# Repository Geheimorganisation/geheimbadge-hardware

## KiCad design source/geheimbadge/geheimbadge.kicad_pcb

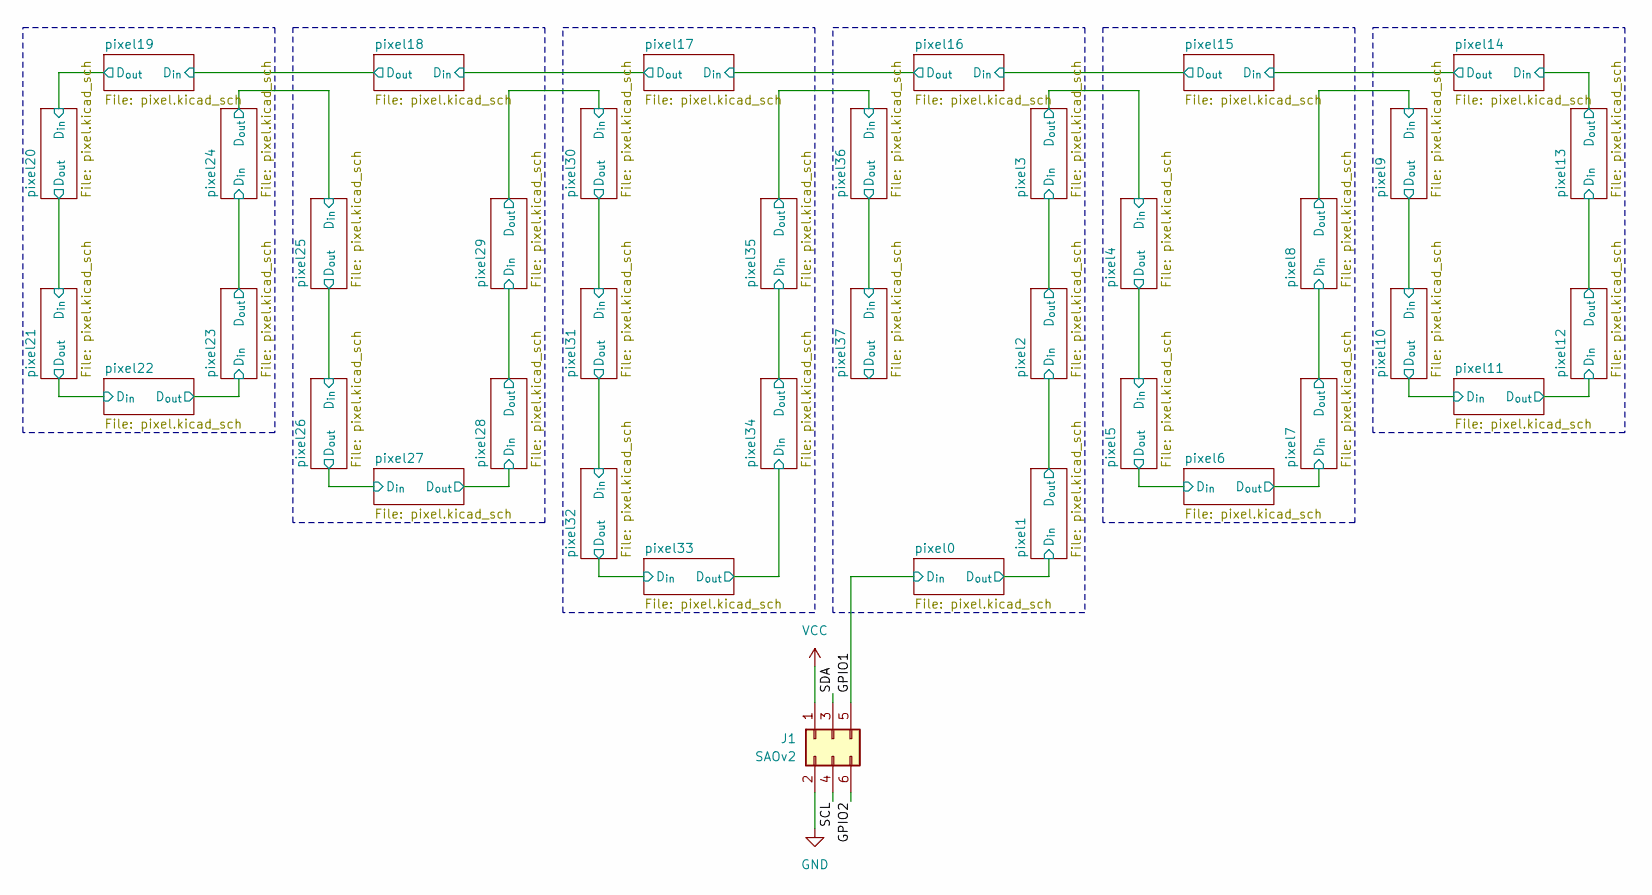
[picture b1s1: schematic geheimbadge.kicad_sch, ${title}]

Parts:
J1: SAOv2; IDC-Header_2x03_P2.54mm_Vertical_SMD; LCSC C4749176

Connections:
/GPIO1: J1.5; also elsewhere on the board
/GPIO2: J1.6
/SCL: J1.4
/SDA: J1.3
GND: J1.2; also elsewhere on the board
VCC: J1.1; also elsewhere on the board

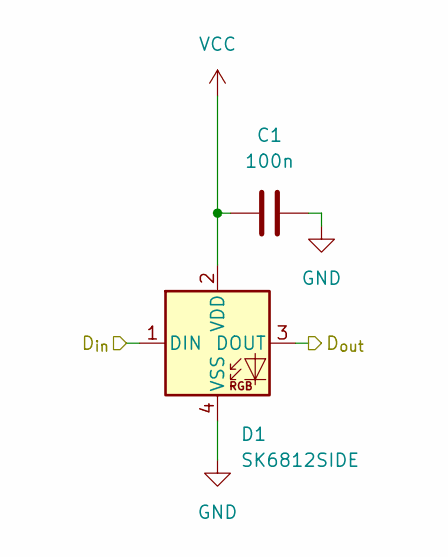
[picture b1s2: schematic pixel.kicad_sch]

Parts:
C1: 100n; C_0402_1005Metric; LCSC C1525
D1: SK6812SIDE; LED-SMD_4P-L4.0-W1.6-L; LCSC C5378721

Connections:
/GPIO1: D1.1 (DIN); also elsewhere on the board
/pixel0/D_{out}: D1.3 (DOUT); also elsewhere on the board
GND: C1.2, D1.4 (VSS); also elsewhere on the board
VCC: C1.1, D1.2 (VDD); also elsewhere on the board

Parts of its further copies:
C2, C3, C4, C5, C6, C7, C8, C9, C10, C11, C12, C13, C14, C15, C16, C17, C18, C19, C20, C21, C22, C23, C24, C25, C26, C27, C28, C29, C30, C31, C32, C33, C34, C35, C36, C37, C38: 100n; C_0402_1005Metric; LCSC C1525
D2, D3, D4, D5, D6, D7, D8, D9, D10, D11, D12, D13, D14, D15, D16, D17, D18, D19, D20, D21, D22, D23, D24, D25, D26, D27, D28, D29, D30, D31, D32, D33, D34, D35, D36, D37, D38: SK6812SIDE; LED-SMD_4P-L4.0-W1.6-L; LCSC C5378721

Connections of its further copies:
/pixel0/D_{out}: D2.1 (DIN); also elsewhere on the board
/pixel1/D_{out}: D2.3 (DOUT), D3.1 (DIN)
/pixel2/D_{out}: D3.3 (DOUT), D4.1 (DIN)
/pixel3/D_{out}: D4.3 (DOUT), D5.1 (DIN)
/pixel4/D_{out}: D5.3 (DOUT), D6.1 (DIN)
/pixel5/D_{out}: D6.3 (DOUT), D7.1 (DIN)
/pixel6/D_{out}: D7.3 (DOUT), D8.1 (DIN)
/pixel7/D_{out}: D8.3 (DOUT), D9.1 (DIN)
/pixel8/D_{out}: D9.3 (DOUT), D10.1 (DIN)
/pixel10/D_{in}: D10.3 (DOUT), D11.1 (DIN)
/pixel10/D_{out}: D11.3 (DOUT), D12.1 (DIN)
/pixel11/D_{out}: D12.3 (DOUT), D13.1 (DIN)
/pixel12/D_{out}: D13.3 (DOUT), D14.1 (DIN)
/pixel13/D_{out}: D14.3 (DOUT), D15.1 (DIN)
/pixel14/D_{out}: D15.3 (DOUT), D16.1 (DIN)
/pixel15/D_{out}: D16.3 (DOUT), D17.1 (DIN)
/pixel16/D_{out}: D17.3 (DOUT), D18.1 (DIN)
/pixel17/D_{out}: D18.3 (DOUT), D19.1 (DIN)
/pixel18/D_{out}: D19.3 (DOUT), D20.1 (DIN)
/pixel19/D_{out}: D20.3 (DOUT), D21.1 (DIN)
/pixel20/D_{out}: D21.3 (DOUT), D22.1 (DIN)
/pixel21/D_{out}: D22.3 (DOUT), D23.1 (DIN)
/pixel22/D_{out}: D23.3 (DOUT), D24.1 (DIN)
/pixel23/D_{out}: D24.3 (DOUT), D25.1 (DIN)
/pixel24/D_{out}: D25.3 (DOUT), D26.1 (DIN)
/pixel25/D_{out}: D26.3 (DOUT), D27.1 (DIN)
/pixel26/D_{out}: D27.3 (DOUT), D28.1 (DIN)
/pixel27/D_{out}: D28.3 (DOUT), D29.1 (DIN)
/pixel28/D_{out}: D29.3 (DOUT), D30.1 (DIN)
/pixel29/D_{out}: D30.3 (DOUT), D31.1 (DIN)
/pixel30/D_{out}: D31.3 (DOUT), D32.1 (DIN)
/pixel31/D_{out}: D32.3 (DOUT), D33.1 (DIN)
/pixel32/D_{out}: D33.3 (DOUT), D34.1 (DIN)
/pixel33/D_{out}: D34.3 (DOUT), D35.1 (DIN)
/pixel34/D_{out}: D35.3 (DOUT), D36.1 (DIN)
/pixel35/D_{out}: D36.3 (DOUT), D37.1 (DIN)
/pixel36/D_{out}: D37.3 (DOUT), D38.1 (DIN)
/pixel37/D_{out}: D38.3 (DOUT)
GND: C2.2, C3.2, C4.2, C5.2, C6.2, C7.2, C8.2, C9.2, C10.2, C11.2, C12.2, C13.2, C14.2, C15.2, C16.2, C17.2, C18.2, C19.2, C20.2, C21.2, C22.2, C23.2, C24.2, C25.2, C26.2, C27.2, C28.2, C29.2, C30.2, C31.2, C32.2, C33.2, C34.2, C35.2, C36.2, C37.2, C38.2, D2.4 (VSS), D3.4 (VSS), D4.4 (VSS), D5.4 (VSS), D6.4 (VSS), D7.4 (VSS), D8.4 (VSS), D9.4 (VSS), D10.4 (VSS), D11.4 (VSS), D12.4 (VSS), D13.4 (VSS), D14.4 (VSS), D15.4 (VSS), D16.4 (VSS), D17.4 (VSS), D18.4 (VSS), D19.4 (VSS), D20.4 (VSS), D21.4 (VSS), D22.4 (VSS), D23.4 (VSS), D24.4 (VSS), D25.4 (VSS), D26.4 (VSS), D27.4 (VSS), D28.4 (VSS), D29.4 (VSS), D30.4 (VSS), D31.4 (VSS), D32.4 (VSS), D33.4 (VSS), D34.4 (VSS), D35.4 (VSS), D36.4 (VSS), D37.4 (VSS), D38.4 (VSS); also elsewhere on the board
VCC: C2.1, C3.1, C4.1, C5.1, C6.1, C7.1, C8.1, C9.1, C10.1, C11.1, C12.1, C13.1, C14.1, C15.1, C16.1, C17.1, C18.1, C19.1, C20.1, C21.1, C22.1, C23.1, C24.1, C25.1, C26.1, C27.1, C28.1, C29.1, C30.1, C31.1, C32.1, C33.1, C34.1, C35.1, C36.1, C37.1, C38.1, D2.2 (VDD), D3.2 (VDD), D4.2 (VDD), D5.2 (VDD), D6.2 (VDD), D7.2 (VDD), D8.2 (VDD), D9.2 (VDD), D10.2 (VDD), D11.2 (VDD), D12.2 (VDD), D13.2 (VDD), D14.2 (VDD), D15.2 (VDD), D16.2 (VDD), D17.2 (VDD), D18.2 (VDD), D19.2 (VDD), D20.2 (VDD), D21.2 (VDD), D22.2 (VDD), D23.2 (VDD), D24.2 (VDD), D25.2 (VDD), D26.2 (VDD), D27.2 (VDD), D28.2 (VDD), D29.2 (VDD), D30.2 (VDD), D31.2 (VDD), D32.2 (VDD), D33.2 (VDD), D34.2 (VDD), D35.2 (VDD), D36.2 (VDD), D37.2 (VDD), D38.2 (VDD); also elsewhere on the board

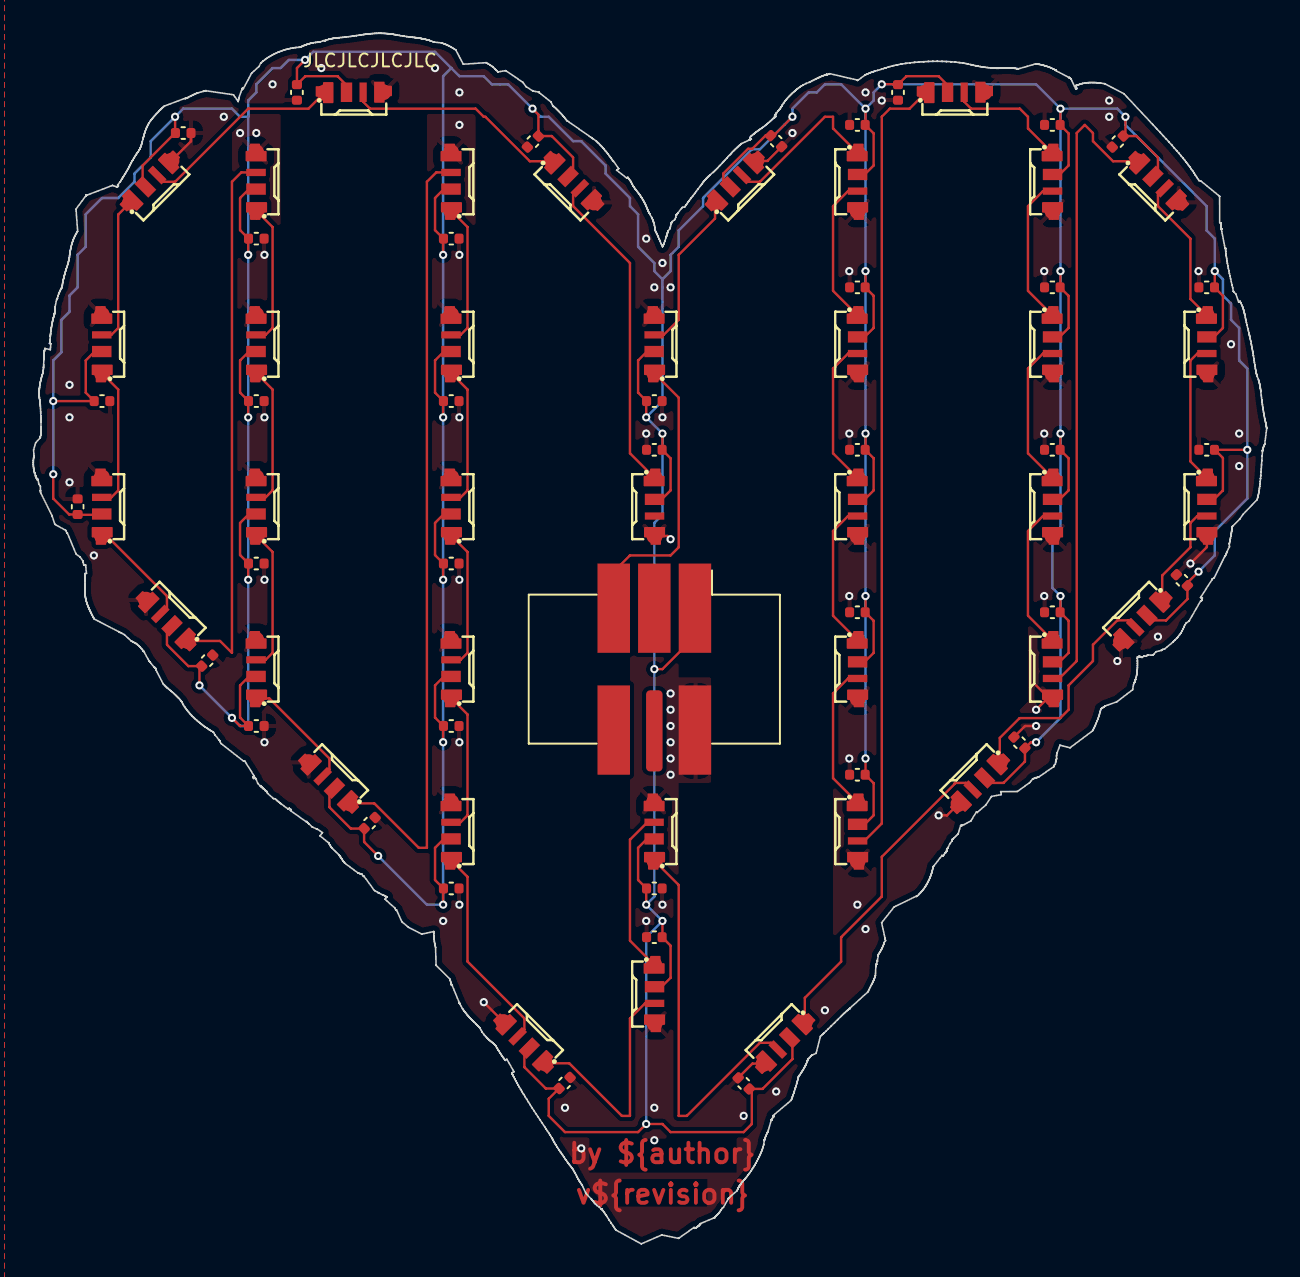
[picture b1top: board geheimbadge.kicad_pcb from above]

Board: 2 copper layers, 75.9 x 74.5 mm, 77 parts (0 on the bottom side), 40 nets.

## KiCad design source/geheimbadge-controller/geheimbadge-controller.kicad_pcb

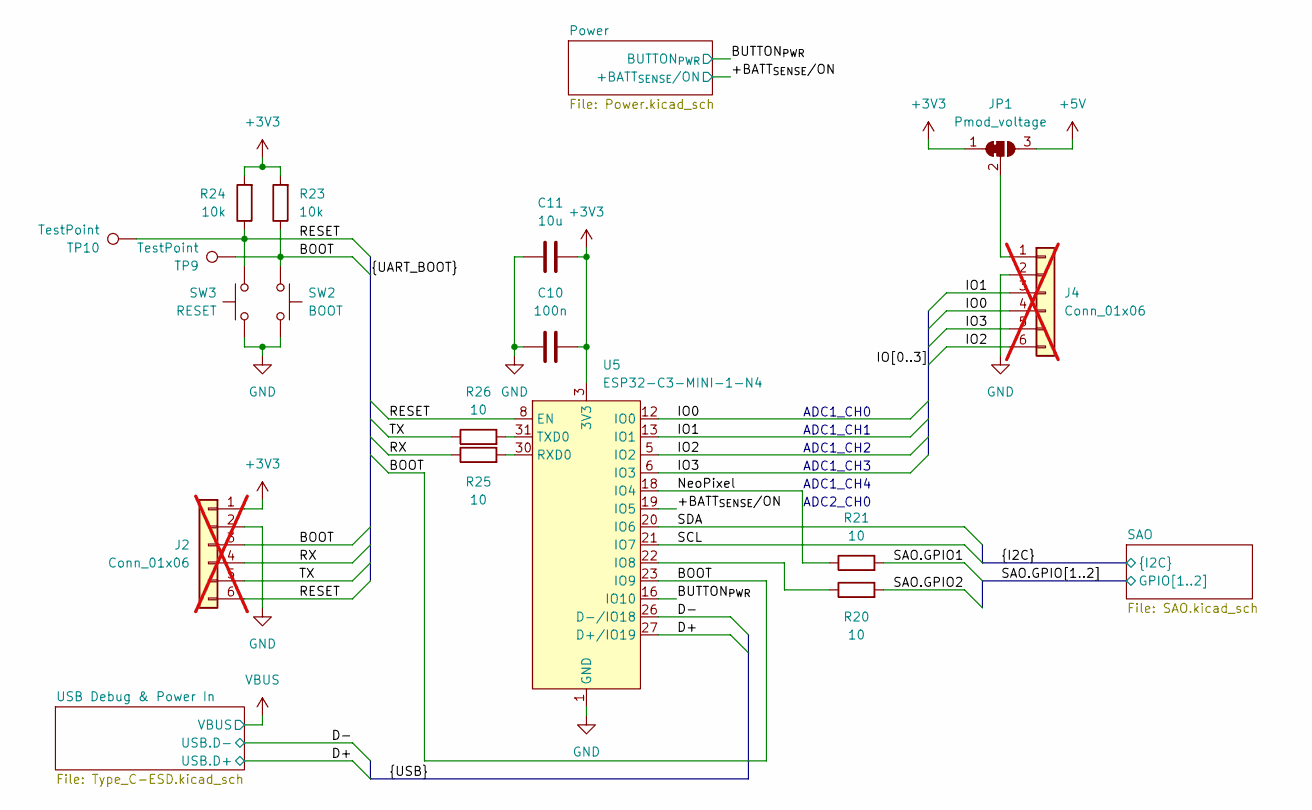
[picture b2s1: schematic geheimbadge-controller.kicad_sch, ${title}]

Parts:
C10: 100n; C_0603_1608Metric; LCSC Part C14663
C11: 10u; C_0805_2012Metric; LCSC Part C15850
J2, J4: Conn_01x06; PinSocket_1x06_P2.54mm_Horizontal; not fitted
JP1: Pmod_voltage; SolderJumper-3_P1.3mm_Bridged12_RoundedPad1.0x1.5mm
R20, R21, R25, R26: 10; R_0603_1608Metric; LCSC Part C22859
R23, R24: 10k; R_0603_1608Metric; LCSC Part C25804
SW2: BOOT; SW_Push_1P1T_XKB_TS-1187A; LCSC Part C318884
SW3: RESET; SW_Push_1P1T_XKB_TS-1187A; LCSC Part C318884
TP9, TP10: TestPoint; TestPoint_Pad_D1.0mm
U5: ESP32-C3-MINI-1-N4; WIFIM-SMD_ESP32-C3-MINI-1; LCSC Part C2838502

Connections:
+3V3: C10.1, C11.1, J2.1, JP1.1 (A), R23.2, R24.2, U5.3 (3V3); also elsewhere on the board
+5V: JP1.3 (B); also elsewhere on the board
/+BATT_{SENSE}/ON: U5.19 (IO5); also elsewhere on the board
/BOOT: J2.3, R23.1, SW2.2, TP9.1, U5.23 (IO9)
/BUTTON_{PWR}: U5.16 (IO10); also elsewhere on the board
/D+: U5.27 (D+/IO19); also elsewhere on the board
/D-: U5.26 (D-/IO18); also elsewhere on the board
/IO0: J4.4, U5.12 (IO0)
/IO1: J4.3, U5.13 (IO1)
/IO2: J4.6, U5.5 (IO2)
/IO3: J4.5, U5.6 (IO3)
/NeoPixel: R21.1, U5.18 (IO4)
/RESET: J2.6, R24.1, SW3.2, TP10.1, U5.8 (EN)
/RX: J2.4, R25.1
/SAO.GPIO1: R21.2; also elsewhere on the board
/SAO.GPIO2: R20.2; also elsewhere on the board
/SCL: U5.21 (IO7); also elsewhere on the board
/SDA: U5.20 (IO6); also elsewhere on the board
/TX: J2.5, R26.1
GND: C10.2, C11.2, J2.2, J4.2, SW2.1, SW3.1, U5.1 (GND), U5.2 (GND), U5.11 (GND), U5.14 (GND), U5.36 (GND), U5.37 (GND), U5.38 (GND), U5.39 (GND), U5.40 (GND), U5.41 (GND), U5.42 (GND), U5.43 (GND), U5.44 (GND), U5.45 (GND), U5.46 (GND), U5.47 (GND), U5.48 (GND), U5.49 (GND), U5.50 (GND), U5.51 (GND), U5.52 (GND), U5.53 (GND); also elsewhere on the board
unnamed: J4.1, JP1.2 (C)
unnamed: R20.1, U5.22 (IO8)
unnamed: R25.2, U5.30 (RXD0)
unnamed: R26.2, U5.31 (TXD0)

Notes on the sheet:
ADC2_CH0
ADC1_CH2
ADC1_CH1
ADC1_CH3
ADC1_CH0
ADC1_CH4

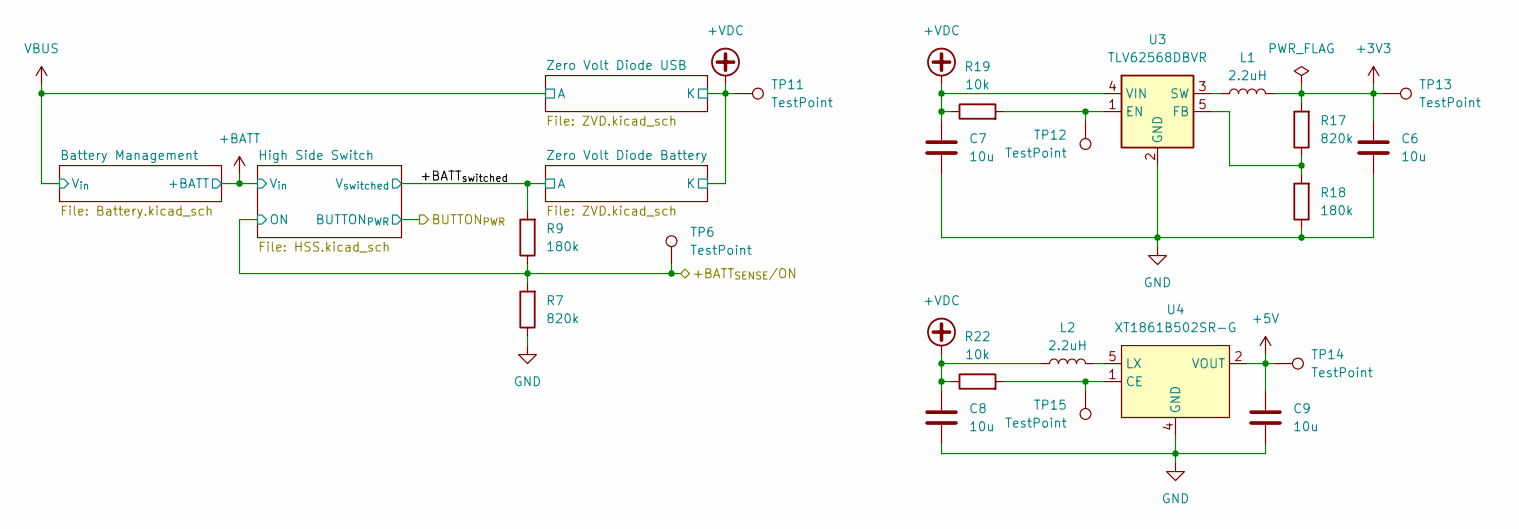
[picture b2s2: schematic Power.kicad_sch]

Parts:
C6, C7, C8, C9: 10u; C_0805_2012Metric; LCSC Part C15850
L1, L2: 2.2uH; L_1008_2520Metric; LCSC Part C3040393
R7, R17: 820k; R_0603_1608Metric; LCSC Part C23252
R9, R18: 180k; R_0603_1608Metric; LCSC Part C22827
R19, R22: 10k; R_0603_1608Metric; LCSC Part C25804
TP6, TP11, TP12, TP13, TP14, TP15: TestPoint; TestPoint_Pad_D1.0mm
U3: TLV62568DBVR; SOT-23-5; LCSC Part C163219
U4: XT1861B502SR-G; SOT-23-5; LCSC Part C3008013

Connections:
+3V3: C6.2, L1.2, R17.2, TP13.1; also elsewhere on the board
+5V: C9.2, TP14.1, U4.2 (VOUT); also elsewhere on the board
+VDC: C7.2, C8.2, L2.1, R19.1, R22.1, TP11.1, U3.4 (VIN); also elsewhere on the board
/+BATT_{SENSE}/ON: R7.2, R9.1, TP6.1; also elsewhere on the board
/Power/+BATT_{switched}: R9.2; also elsewhere on the board
GND: C6.1, C7.1, C8.1, C9.1, R7.1, R18.1, U3.2 (GND), U4.4 (GND); also elsewhere on the board
unnamed: R19.2, TP12.1, U3.1 (EN)
unnamed: R17.1, R18.2, U3.5 (FB)
unnamed: L1.1, U3.3 (SW)
unnamed: R22.2, TP15.1, U4.1 (CE)
unnamed: L2.2, U4.5 (LX)

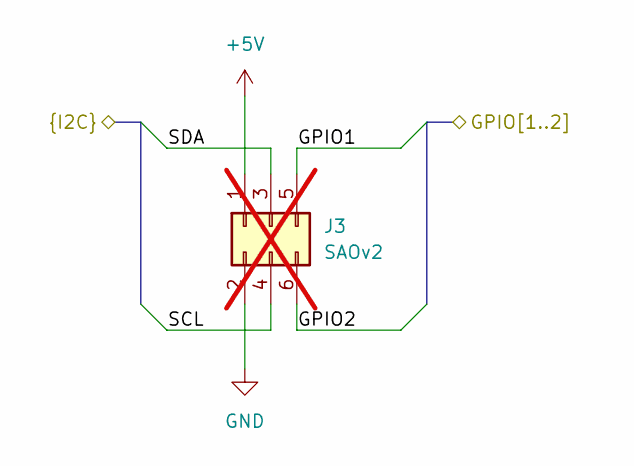
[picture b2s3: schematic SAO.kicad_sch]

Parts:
J3: SAOv2; PinSocket_2x03_P2.54mm_Vertical; LCSC Part C4749176; not fitted

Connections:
+5V: J3.1; also elsewhere on the board
/SAO.GPIO1: J3.5; also elsewhere on the board
/SAO.GPIO2: J3.6; also elsewhere on the board
/SCL: J3.4; also elsewhere on the board
/SDA: J3.3; also elsewhere on the board
GND: J3.2; also elsewhere on the board

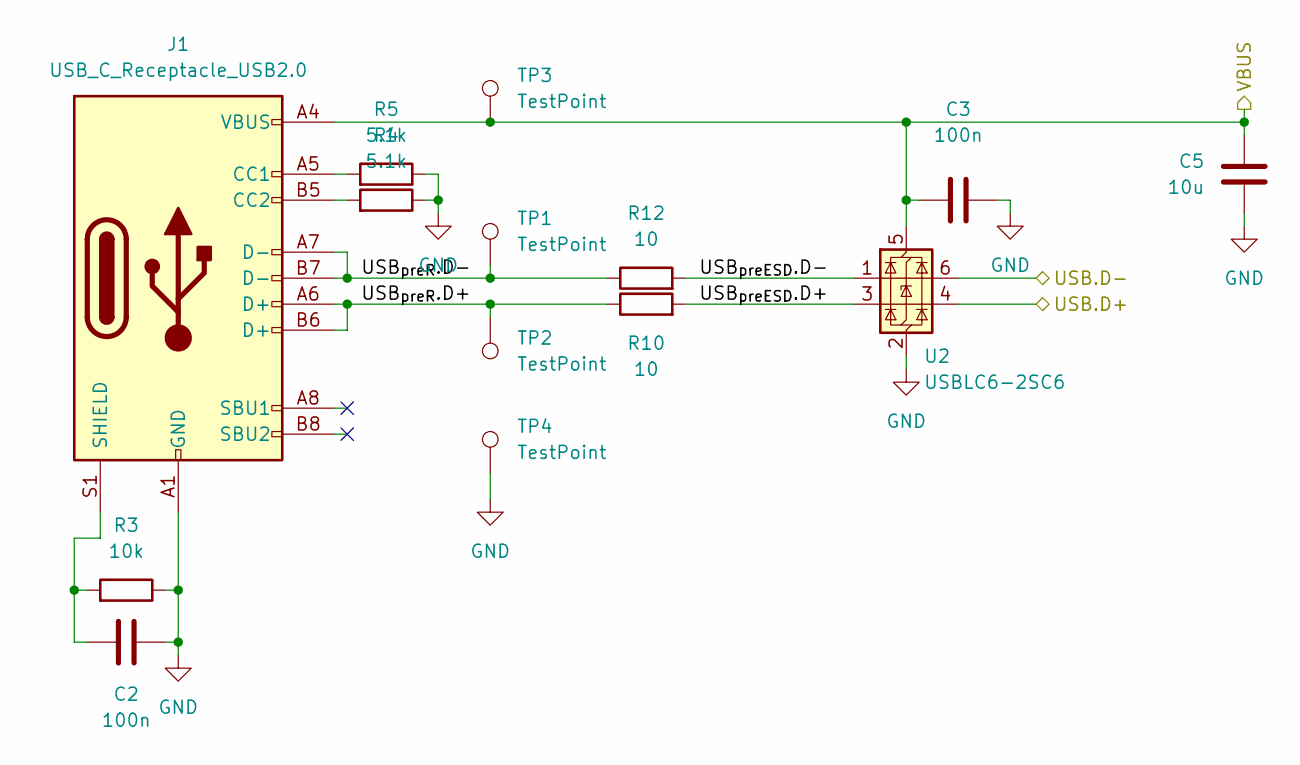
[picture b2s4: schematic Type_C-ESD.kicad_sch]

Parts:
C2, C3: 100n; C_0603_1608Metric; LCSC Part C14663
C5: 10u; C_0805_2012Metric; LCSC Part C15850
J1: USB_C_Receptacle_USB2.0; USB_C_Receptacle_HRO_TYPE-C-31-M-12; LCSC Part C2765186
R3: 10k; R_0603_1608Metric; LCSC Part C25804
R4, R5: 5.1k; R_0603_1608Metric; LCSC Part C23186
R10, R12: 10; R_0603_1608Metric; LCSC Part C22859
TP1, TP2, TP3, TP4: TestPoint; TestPoint_Pad_D1.0mm
U2: USBLC6-2SC6; SOT-23-6; LCSC Part C2827654

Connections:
/D+: U2.4 (I/O2); also elsewhere on the board
/D-: U2.6 (I/O1); also elsewhere on the board
/USB Debug & Power In/USB_{preESD}.D+: R10.2, U2.3 (I/O2)
/USB Debug & Power In/USB_{preESD}.D-: R12.2, U2.1 (I/O1)
/USB Debug & Power In/USB_{preR}.D+: J1.A6 (D+), J1.B6 (D+), R10.1, TP2.1
/USB Debug & Power In/USB_{preR}.D-: J1.A7 (D-), J1.B7 (D-), R12.1, TP1.1
GND: C2.2, C3.2, C5.1, J1.A1 (GND), J1.A12 (GND), J1.B1 (GND), J1.B12 (GND), R3.1, R4.1, R5.1, TP4.1, U2.2 (GND); also elsewhere on the board
unnamed: J1.A5 (CC1), R5.2
unnamed: J1.B5 (CC2), R4.2
unnamed: C2.1, J1.S1 (SHIELD), R3.2
VBUS: C3.1, C5.2, J1.A4 (VBUS), J1.A9 (VBUS), J1.B4 (VBUS), J1.B9 (VBUS), TP3.1, U2.5 (VBUS); also elsewhere on the board

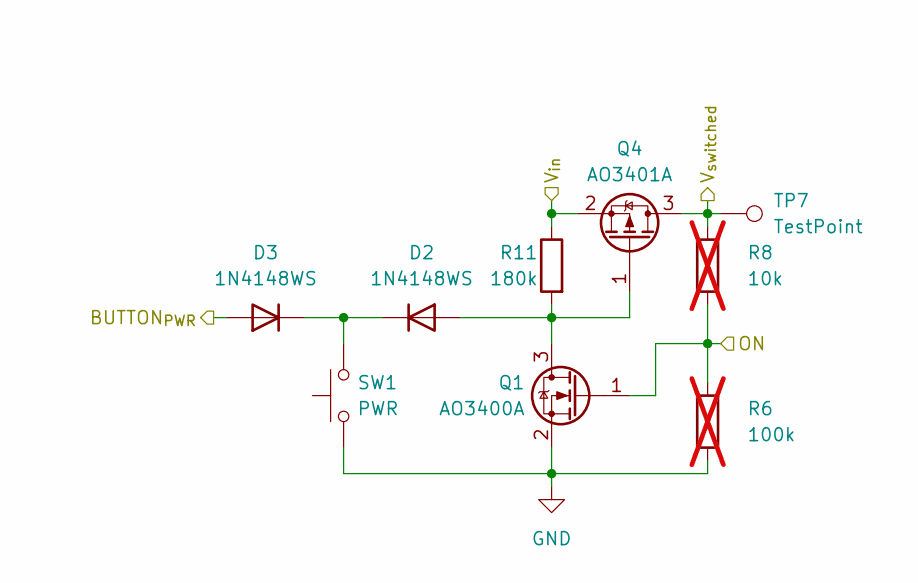
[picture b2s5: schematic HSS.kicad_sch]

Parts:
D2, D3: 1N4148WS; D_SOD-323; LCSC Part C2128
Q1: AO3400A; SOT-23; LCSC Part C20917
Q4: AO3401A; SOT-23; LCSC Part C15127
R6: 100k; R_0603_1608Metric; not fitted
R8: 10k; R_0603_1608Metric; not fitted
R11: 180k; R_0603_1608Metric; LCSC Part C22827
SW1: PWR; SW_Push_1P1T_XKB_TS-1187A; LCSC Part C318884
TP7: TestPoint; TestPoint_Pad_D1.0mm

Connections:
+BATT: Q4.2 (S), R11.1; also elsewhere on the board
/+BATT_{SENSE}/ON: Q1.1 (G), R6.1, R8.1; also elsewhere on the board
/BUTTON_{PWR}: D3.2 (A); also elsewhere on the board
/Power/+BATT_{switched}: Q4.3 (D), R8.2, TP7.1; also elsewhere on the board
GND: Q1.2 (S), R6.2, SW1.1; also elsewhere on the board
unnamed: D2.1 (K), D3.1 (K), SW1.2
unnamed: D2.2 (A), Q1.3 (D), Q4.1 (G), R11.2

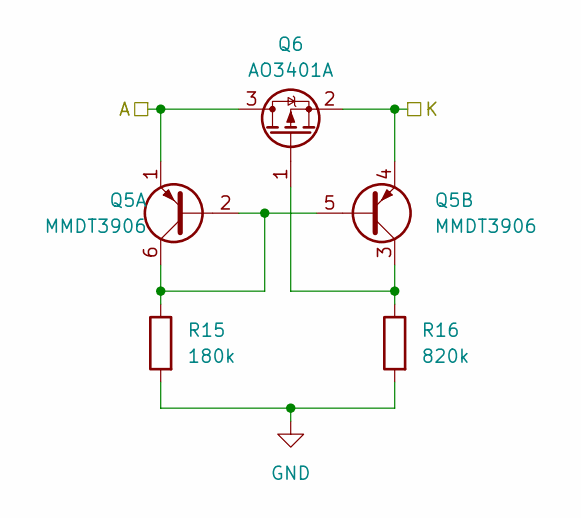
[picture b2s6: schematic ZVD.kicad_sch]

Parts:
Q5: MMDT3906; SOT-363_SC-70-6; LCSC Part C3000398
Q6: AO3401A; SOT-23; LCSC Part C15127
R15: 180k; R_0603_1608Metric; LCSC Part C22827
R16: 820k; R_0603_1608Metric; LCSC Part C23252

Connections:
+VDC: Q5.4 (E2), Q6.2 (S); also elsewhere on the board
/Power/+BATT_{switched}: Q5.1 (E1), Q6.3 (D); also elsewhere on the board
GND: R15.2, R16.2; also elsewhere on the board
unnamed: Q5.2 (B1), Q5.5 (B2), Q5.6 (C1), R15.1
unnamed: Q5.3 (C2), Q6.1 (G), R16.1

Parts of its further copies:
Q2: MMDT3906; SOT-363_SC-70-6; LCSC Part C3000398
Q3: AO3401A; SOT-23; LCSC Part C15127
R13: 180k; R_0603_1608Metric; LCSC Part C22827
R14: 820k; R_0603_1608Metric; LCSC Part C23252

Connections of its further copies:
+VDC: Q2.4 (E2), Q3.2 (S); also elsewhere on the board
GND: R13.2, R14.2; also elsewhere on the board
unnamed: Q2.2 (B1), Q2.5 (B2), Q2.6 (C1), R13.1
unnamed: Q2.3 (C2), Q3.1 (G), R14.1
VBUS: Q2.1 (E1), Q3.3 (D); also elsewhere on the board

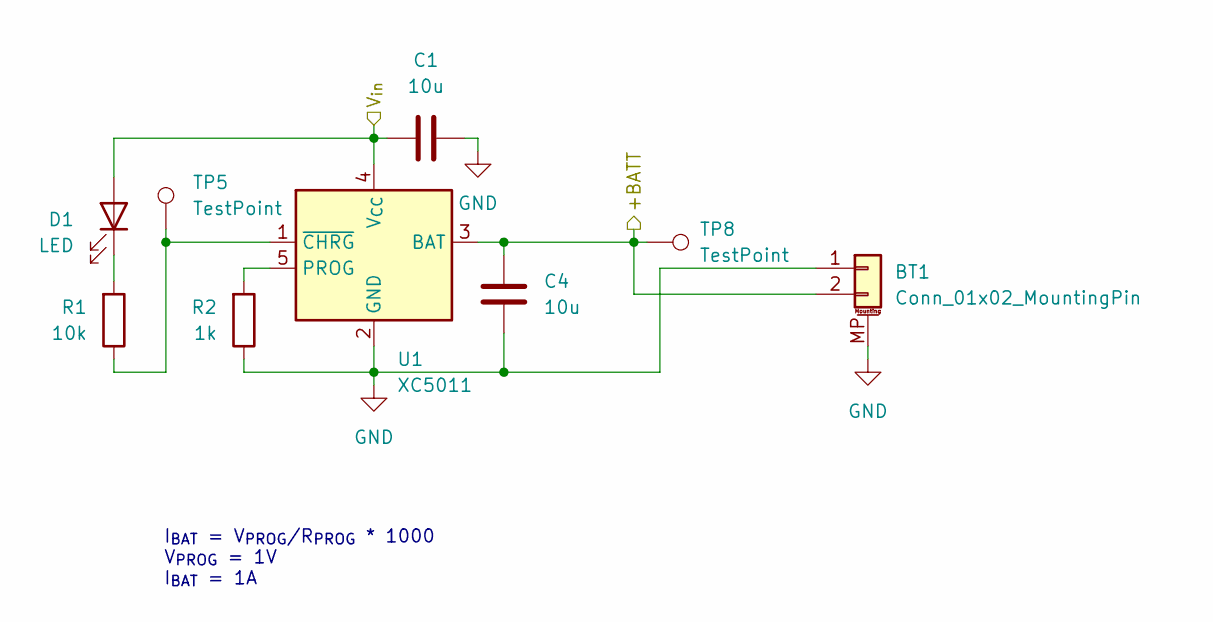
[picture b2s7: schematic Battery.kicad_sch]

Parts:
BT1: Conn_01x02_MountingPin; JST_PH_S2B-PH-SM4-TB_1x02-1MP_P2.00mm_Horizontal; LCSC Part C295747
C1, C4: 10u; C_0805_2012Metric; LCSC Part C15850
D1: LED; LED_0603_1608Metric; LCSC Part C2286
R1: 10k; R_0603_1608Metric; LCSC Part C25804
R2: 1k; R_0603_1608Metric; LCSC Part C21190
TP5, TP8: TestPoint; TestPoint_Pad_D1.0mm
U1: XC5011; TSOT-23-5; LCSC Part C669360

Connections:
+BATT: BT1.2, C4.2, TP8.1, U1.3 (BAT); also elsewhere on the board
GND: BT1.1, BT1.MP (MountPin), C1.1, C4.1, R2.1, U1.2 (GND); also elsewhere on the board
unnamed: D1.1 (K), R1.2
unnamed: R2.2, U1.5 (PROG)
unnamed: R1.1, TP5.1, U1.1 (~CHRG)
VBUS: C1.2, D1.2 (A), U1.4 (V_{CC}); also elsewhere on the board

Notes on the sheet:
I_{BAT} = V_{PROG}/R_{PROG} * 1000 V_{PROG} = 1V I_{BAT} = 1A

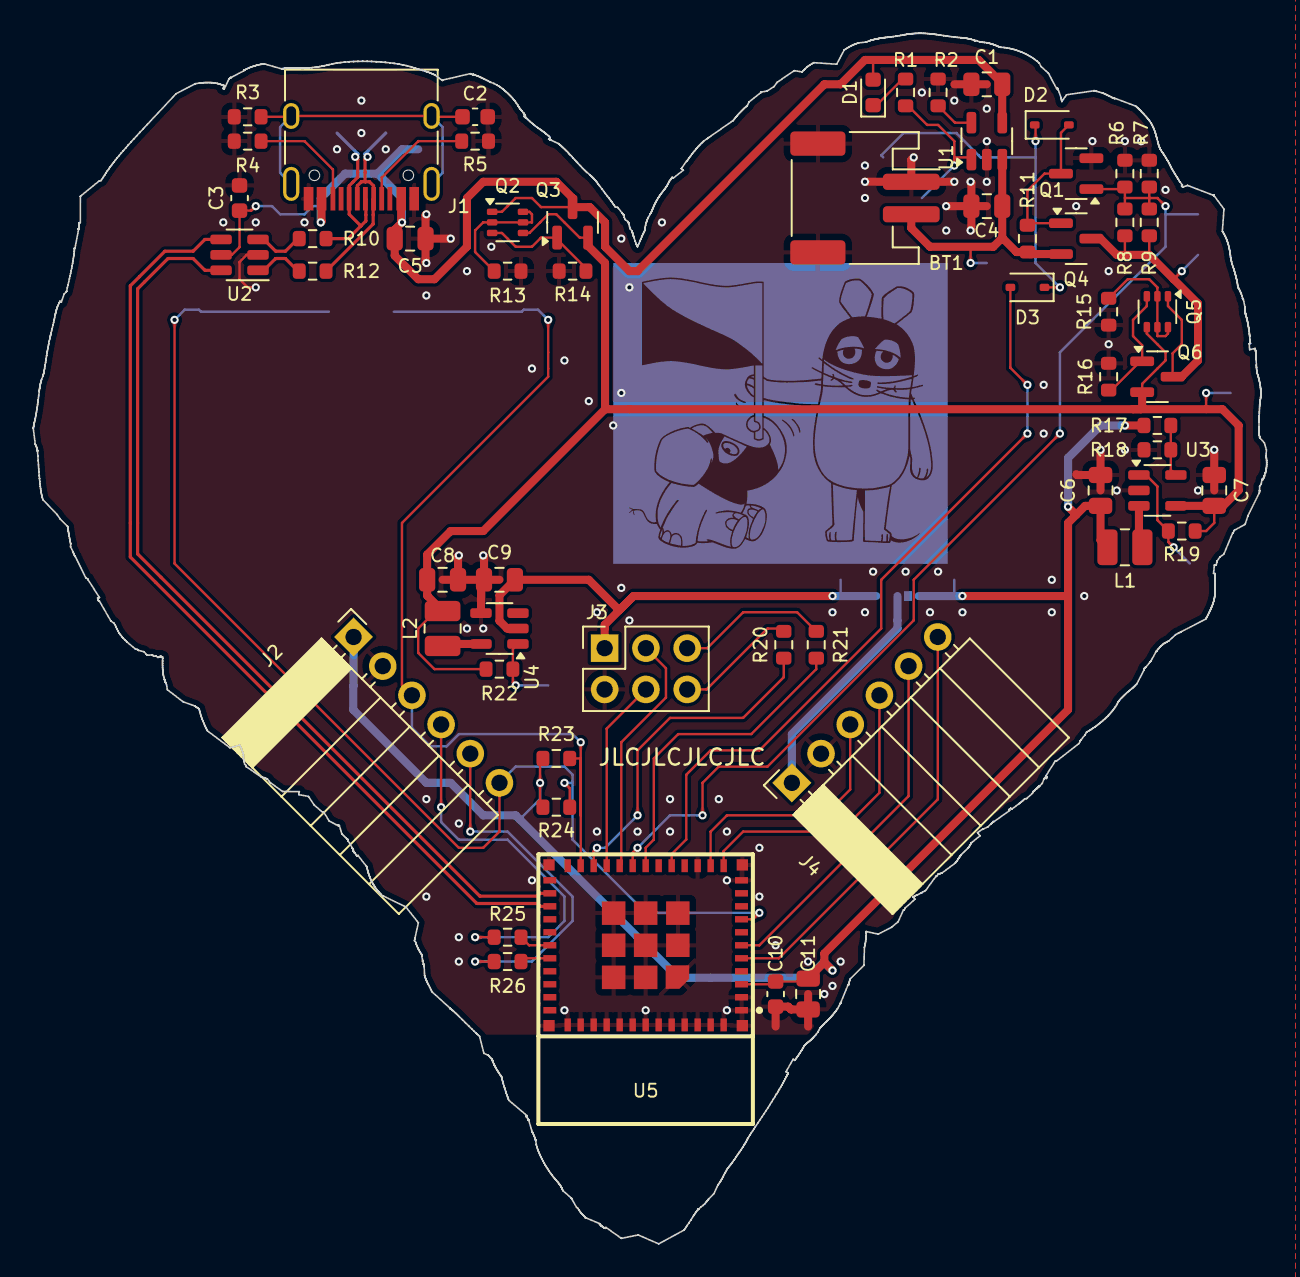
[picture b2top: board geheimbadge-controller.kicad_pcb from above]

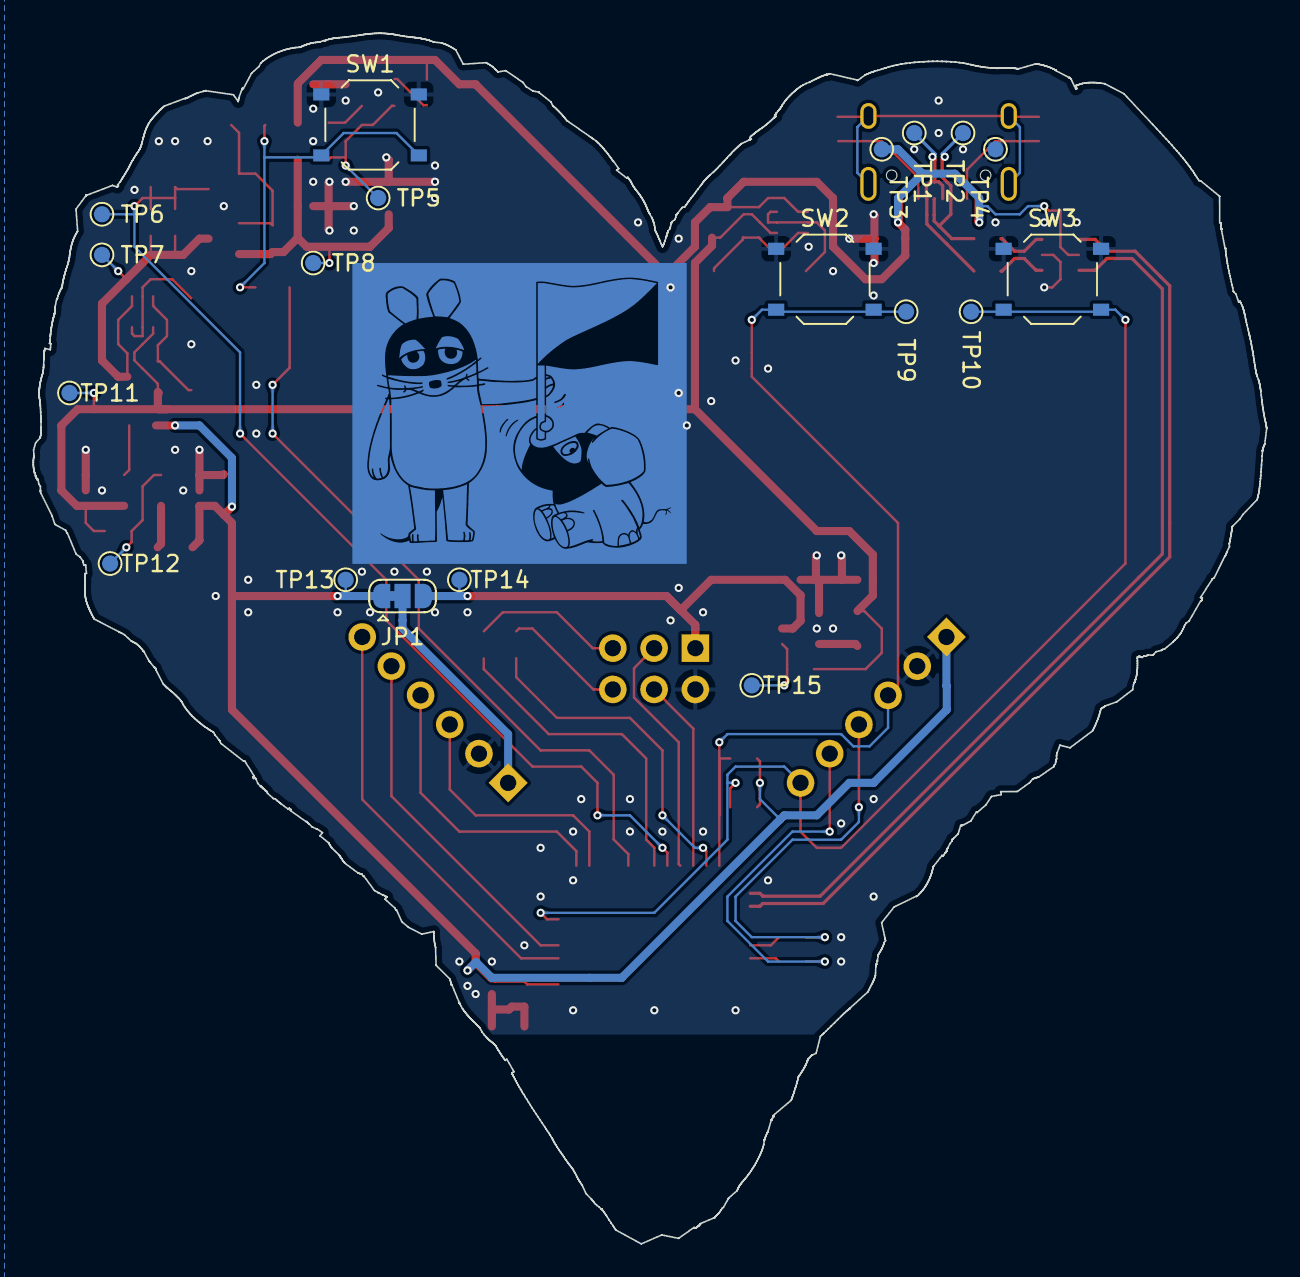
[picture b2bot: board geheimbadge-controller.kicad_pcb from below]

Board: 2 copper layers, 75.9 x 74.5 mm, 77 parts (19 on the bottom side), 49 nets.

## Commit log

2023-10-01 initial design
2023-11-29 new led orientation; no signal resistors
2023-11-30 flipped board
2024-11-13 finalized controller design
2024-12-10 finalized all designs
2024-12-30 add shell
2024-12-30 ignore lock files
2024-12-30 update pixel idices
